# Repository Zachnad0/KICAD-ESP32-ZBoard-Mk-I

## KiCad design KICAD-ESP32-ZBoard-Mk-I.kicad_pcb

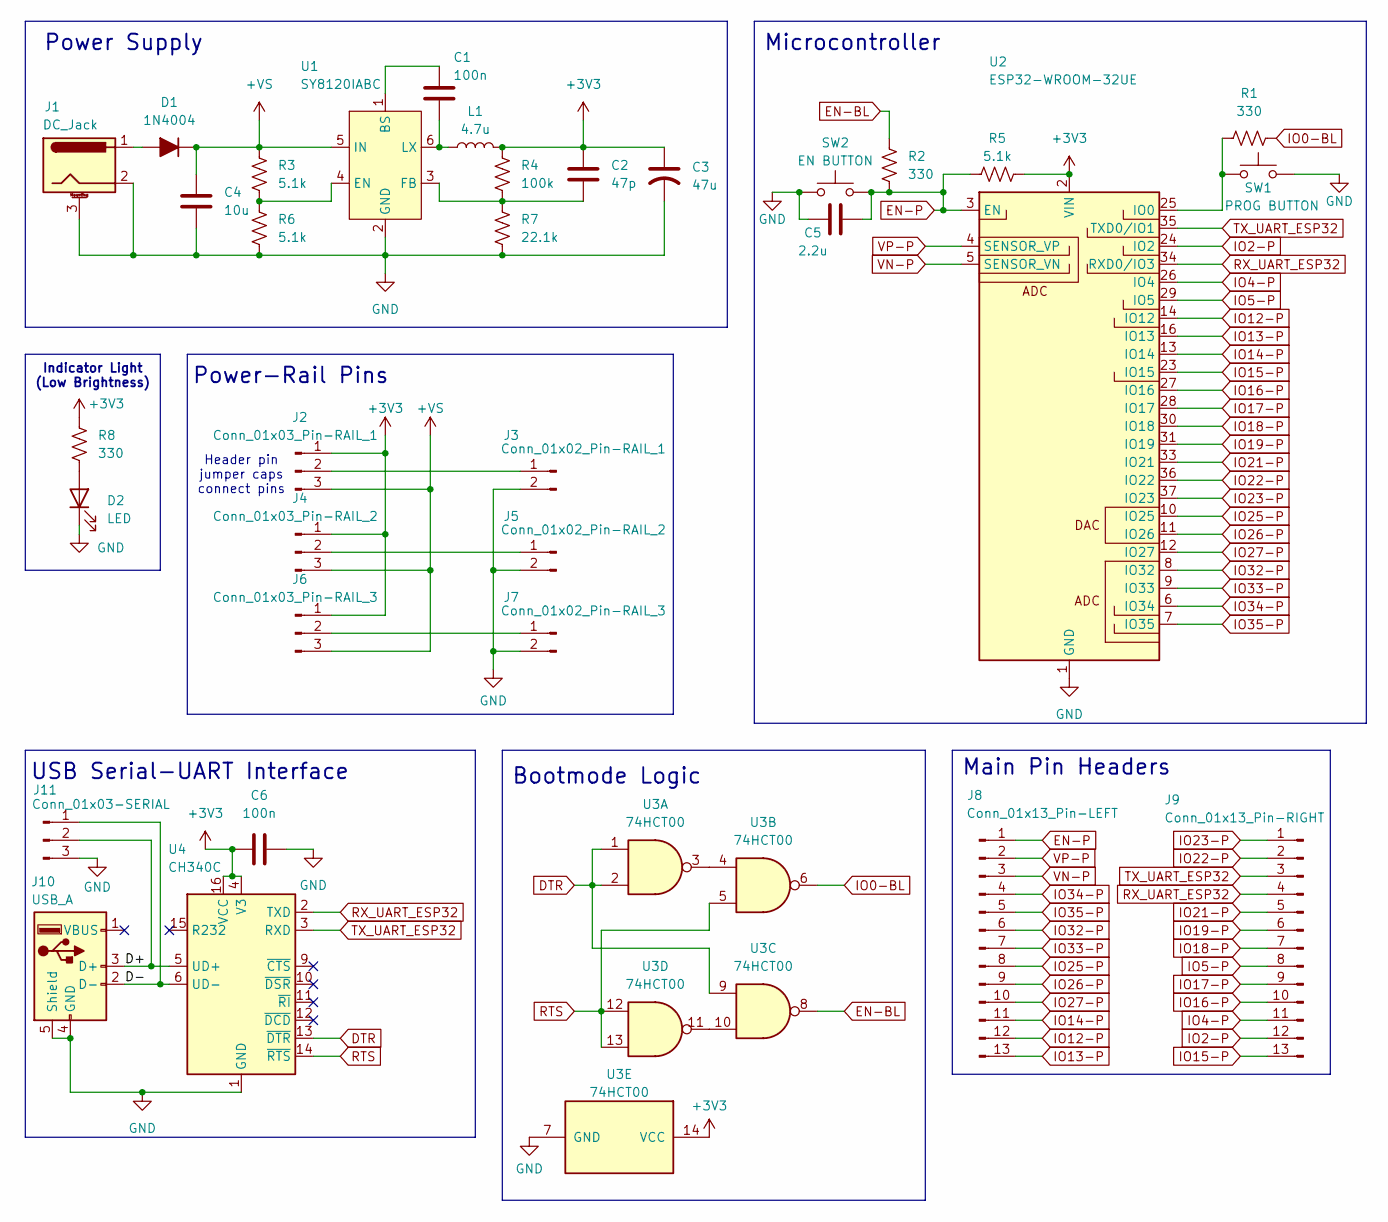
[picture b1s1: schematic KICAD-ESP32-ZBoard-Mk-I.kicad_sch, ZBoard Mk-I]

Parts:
C1, C6: 100n; C_1206_3216Metric_Pad1.33x1.80mm_HandSolder; LCSC Part # C97946
C2: 47p; C_0603_1608Metric_Pad1.08x0.95mm_HandSolder; LCSC Part # C882552
C3: 47u; CP_Radial_D5.0mm_P2.50mm; LCSC Part # n/a
C4: 10u; C_0805_2012Metric_Pad1.18x1.45mm_HandSolder; LCSC Part # C440198
C5: 2.2u; C_0603_1608Metric_Pad1.08x0.95mm_HandSolder; LCSC Part # C415535
D1: 1N4004; D_DO-41_SOD81_P7.62mm_Horizontal; LCSC Part # n/a
D2: LED; D_0603_1608Metric_Pad1.05x0.95mm_HandSolder; LCSC Part # C497928
J1: DC_Jack; BarrelJack_Horizontal; LCSC Part # C720557
J2: Conn_01x03_Pin-RAIL_1; PinHeader_1x03_P2.54mm_Vertical; LCSC Part # n/a
J3: Conn_01x02_Pin-RAIL_1; PinHeader_1x02_P2.54mm_Vertical; LCSC Part # n/a
J4: Conn_01x03_Pin-RAIL_2; PinHeader_1x03_P2.54mm_Vertical; LCSC Part # n/a
J5: Conn_01x02_Pin-RAIL_2; PinHeader_1x02_P2.54mm_Vertical; LCSC Part # n/a
J6: Conn_01x03_Pin-RAIL_3; PinHeader_1x03_P2.54mm_Vertical; LCSC Part # n/a
J7: Conn_01x02_Pin-RAIL_3; PinHeader_1x02_P2.54mm_Vertical; LCSC Part # n/a
J8: Conn_01x13_Pin-LEFT; PinHeader_1x13_P2.54mm_Vertical; LCSC Part # n/a
J9: Conn_01x13_Pin-RIGHT; PinHeader_1x13_P2.54mm_Vertical; LCSC Part # n/a
J10: USB_A; USB-A Jing (C42576); LCSC Part # C42576
J11: Conn_01x03-SERIAL; PinHeader_1x03_P2.54mm_Vertical
L1: 4.7u; L_TDK_SLF7045; LCSC Part # C136201
R1, R2, R8: 330; R_0603_1608Metric; LCSC Part # C384242
R3, R5, R6: 5.1k; R_0603_1608Metric; LCSC Part # C318133
R4: 100k; R_0603_1608Metric; LCSC Part # C25803
R7: 22.1k; R_0603_1608Metric; LCSC Part # C5382621
SW1: PROG BUTTON; SW_101-C-W_XKB; LCSC Part # C318938
SW2: EN BUTTON; SW_101-C-W_XKB; LCSC Part # C318938
U1: SY8120IABC; SOT-23-6; LCSC Part # C479076
U2: ESP32-WROOM-32UE; LCSC Part # C701344
U3: 74HCT00; DIP-14_W7.62mm; LCSC Part # n/a
U4: CH340C; SOP-16_3.9x9.9mm_P1.27mm; LCSC Part # C84681

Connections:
+3V3: C2.1, C3.1, C6.1, J2.1, J4.1, J6.1, L1.2, R4.2, R5.2, R8.1, U2.2 (VIN), U3.14 (VCC), U4.4 (V3), U4.16 (VCC)
+VS: C4.1, D1.1 (K), J2.3, J4.3, J6.3, R3.1, U1.5 (IN)
/D+: J10.3 (D+), J11.2, U4.5 (UD+)
/D-: J10.2 (D-), J11.1, U4.6 (UD-)
DTR: U3.1, U3.2, U3.9, U4.13 (~DTR)
EN-BL: R2.1, U3.8
EN-P: C5.1, J8.1, R2.2, R5.1, SW2.2, U2.3 (EN)
GND: C3.2, C4.2, C5.2, C6.2, D2.1 (K), J1.2, J1.3 (MountPin), J3.2, J5.2, J7.2, J10.4 (GND), J10.5 (Shield), J11.3, R6.2, R7.2, SW1.2, SW2.1, U1.2 (GND), U2.1 (GND), U2.15 (GND), U2.38 (GND), U2.39 (GND), U3.7 (GND), U4.1 (GND)
IO0-BL: R1.2, U3.6
IO2-P: J9.12, U2.24 (IO2)
IO4-P: J9.11, U2.26 (IO4)
IO5-P: J9.8, U2.29 (IO5)
IO12-P: J8.12, U2.14 (IO12)
IO13-P: J8.13, U2.16 (IO13)
IO14-P: J8.11, U2.13 (IO14)
IO15-P: J9.13, U2.23 (IO15)
IO16-P: J9.10, U2.27 (IO16)
IO17-P: J9.9, U2.28 (IO17)
IO18-P: J9.7, U2.30 (IO18)
IO19-P: J9.6, U2.31 (IO19)
IO21-P: J9.5, U2.33 (IO21)
IO22-P: J9.2, U2.36 (IO22)
IO23-P: J9.1, U2.37 (IO23)
IO25-P: J8.8, U2.10 (IO25)
IO26-P: J8.9, U2.11 (IO26)
IO27-P: J8.10, U2.12 (IO27)
IO32-P: J8.6, U2.8 (IO32)
IO33-P: J8.7, U2.9 (IO33)
IO34-P: J8.4, U2.6 (IO34)
IO35-P: J8.5, U2.7 (IO35)
unnamed: D1.2 (A), J1.1
unnamed: D2.2 (A), R8.2
unnamed: J2.2, J3.1
unnamed: J4.2, J5.1
unnamed: J6.2, J7.1
unnamed: C1.1, U1.1 (BS)
unnamed: R3.2, R6.1, U1.4 (EN)
unnamed: C2.2, R4.1, R7.1, U1.3 (FB)
unnamed: C1.2, L1.1, U1.6 (LX)
unnamed: R1.1, SW1.1, U2.25 (IO0)
unnamed: U3.3, U3.4
unnamed: U3.10, U3.11
RTS: U3.5, U3.12, U3.13, U4.14 (~RTS)
RX_UART_ESP32: J9.4, U2.34 (RXD0/IO3), U4.2 (TXD)
TX_UART_ESP32: J9.3, U2.35 (TXD0/IO1), U4.3 (RXD)
VN-P: J8.3, U2.5 (SENSOR_VN)
VP-P: J8.2, U2.4 (SENSOR_VP)

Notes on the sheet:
USB Serial-UART Interface
Indicator Light (Low Brightness)
Power Supply
Header pin jumper caps connect pins
Main Pin Headers
Bootmode Logic
Power-Rail Pins
Microcontroller

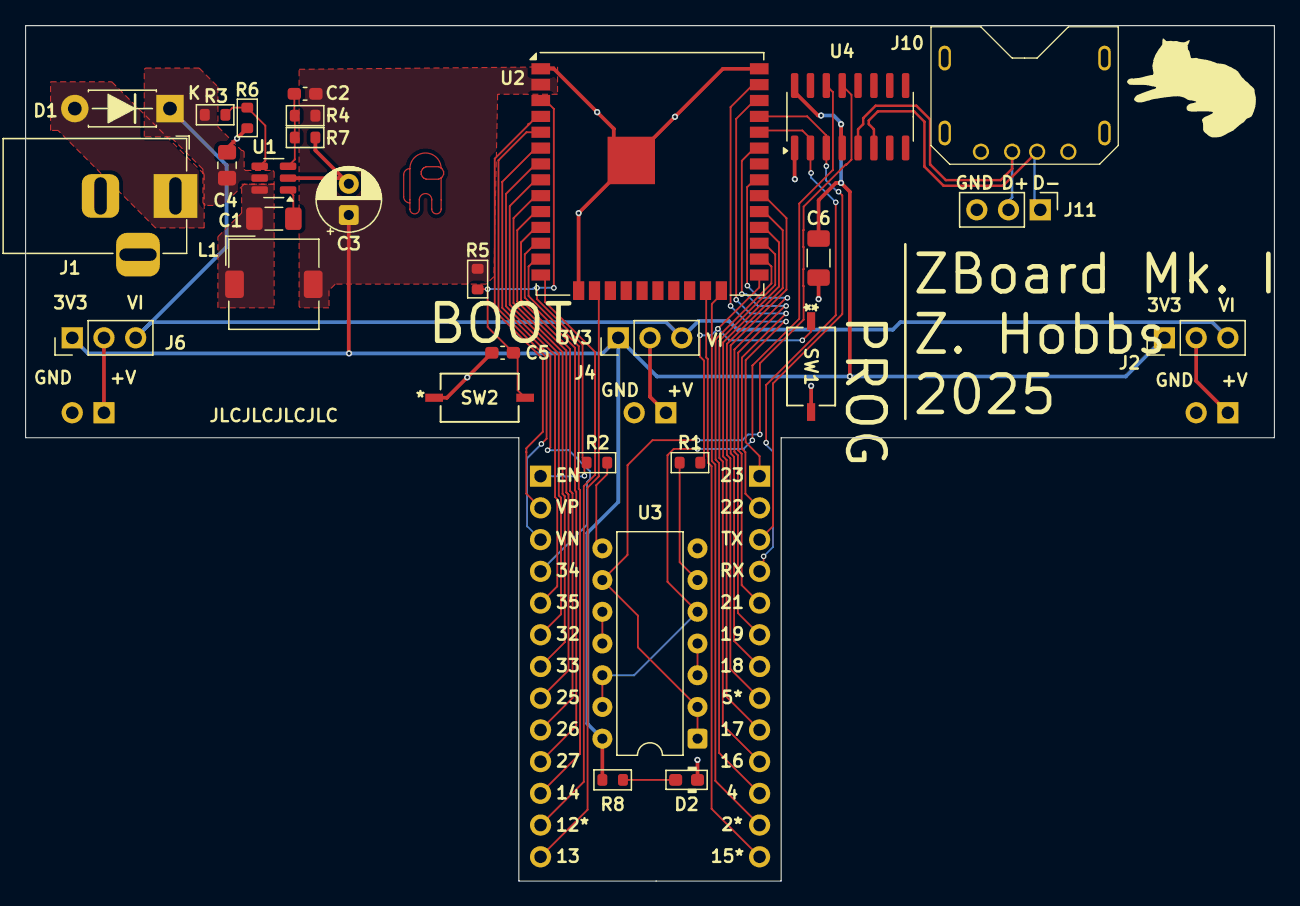
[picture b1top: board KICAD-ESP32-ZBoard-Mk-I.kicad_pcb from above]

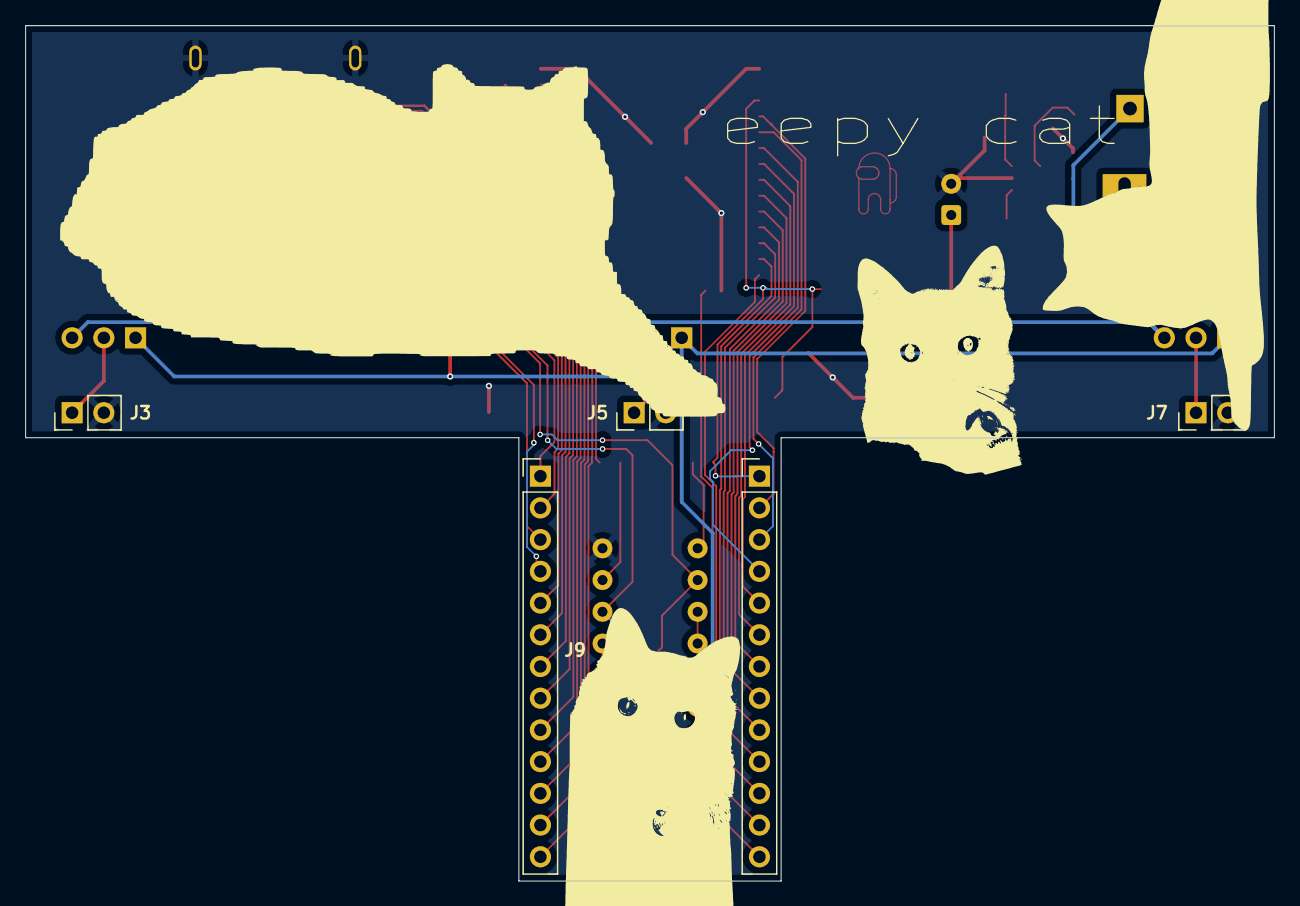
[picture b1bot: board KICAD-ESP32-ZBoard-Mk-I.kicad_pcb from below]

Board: 2 copper layers, 100.0 x 68.5 mm, 35 parts (5 on the bottom side), 47 nets.

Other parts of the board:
FluffGraphic2: LOGO; FluffGraphic2

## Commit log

2025-07-16 Initialized project files.
2025-07-26 ADDED most major ICs for DC power, USB-to-UART, and the ESP32 itself.
2025-08-19 ADDED power supply. ADDED indicator LED.
2025-08-20 ADDED boot mode control logic. ADDED power-rail selection pin headers.
2025-08-25 ADDED main GPIO header pins, each 01x13.
2025-08-27 ADDED all LCSC part numbers and footprint assignments.
2025-08-29 FINISHED footprint placement. ADDED all routes and planes. TODO finalize silkscreen and adding text and graphics.
2025-08-30 ADDED silkscreen text and graphics. FIXED designator text being too small. TODO add header pin labels (very important!).
2025-08-31 ADDED all remaining pin labels. ADDED serial-breakout pins in case alternative USB is wanted.
2025-09-01 ADDED more cat graphics to increase PCB performance by 35%.
2025-09-02 ADDED some text and finalized board.
2025-09-27 Finalized PCB for order.
2025-09-27 Generated BOM for assembly
